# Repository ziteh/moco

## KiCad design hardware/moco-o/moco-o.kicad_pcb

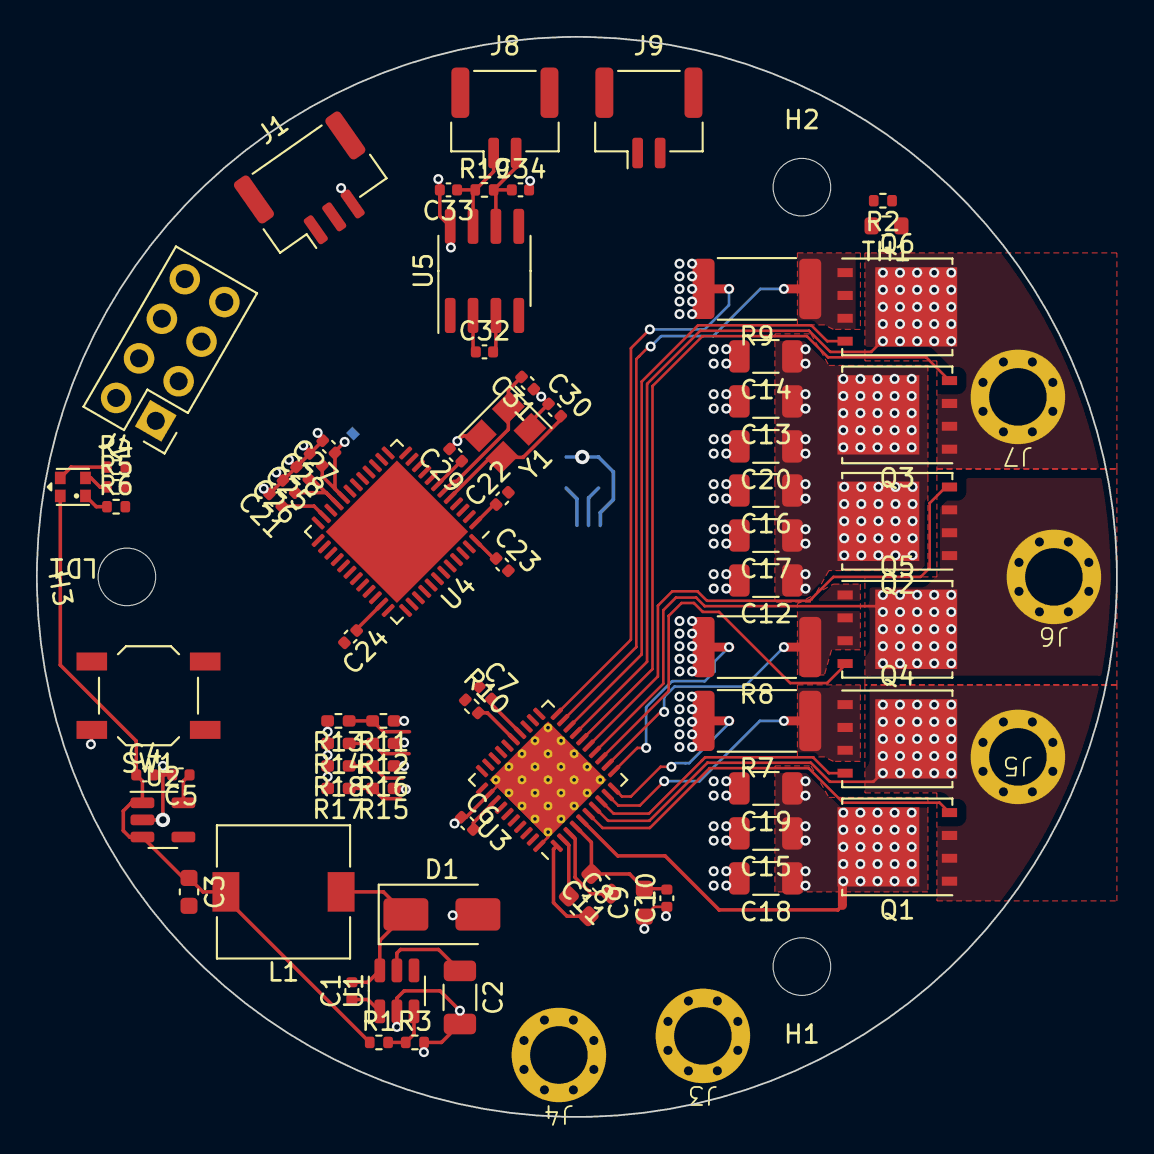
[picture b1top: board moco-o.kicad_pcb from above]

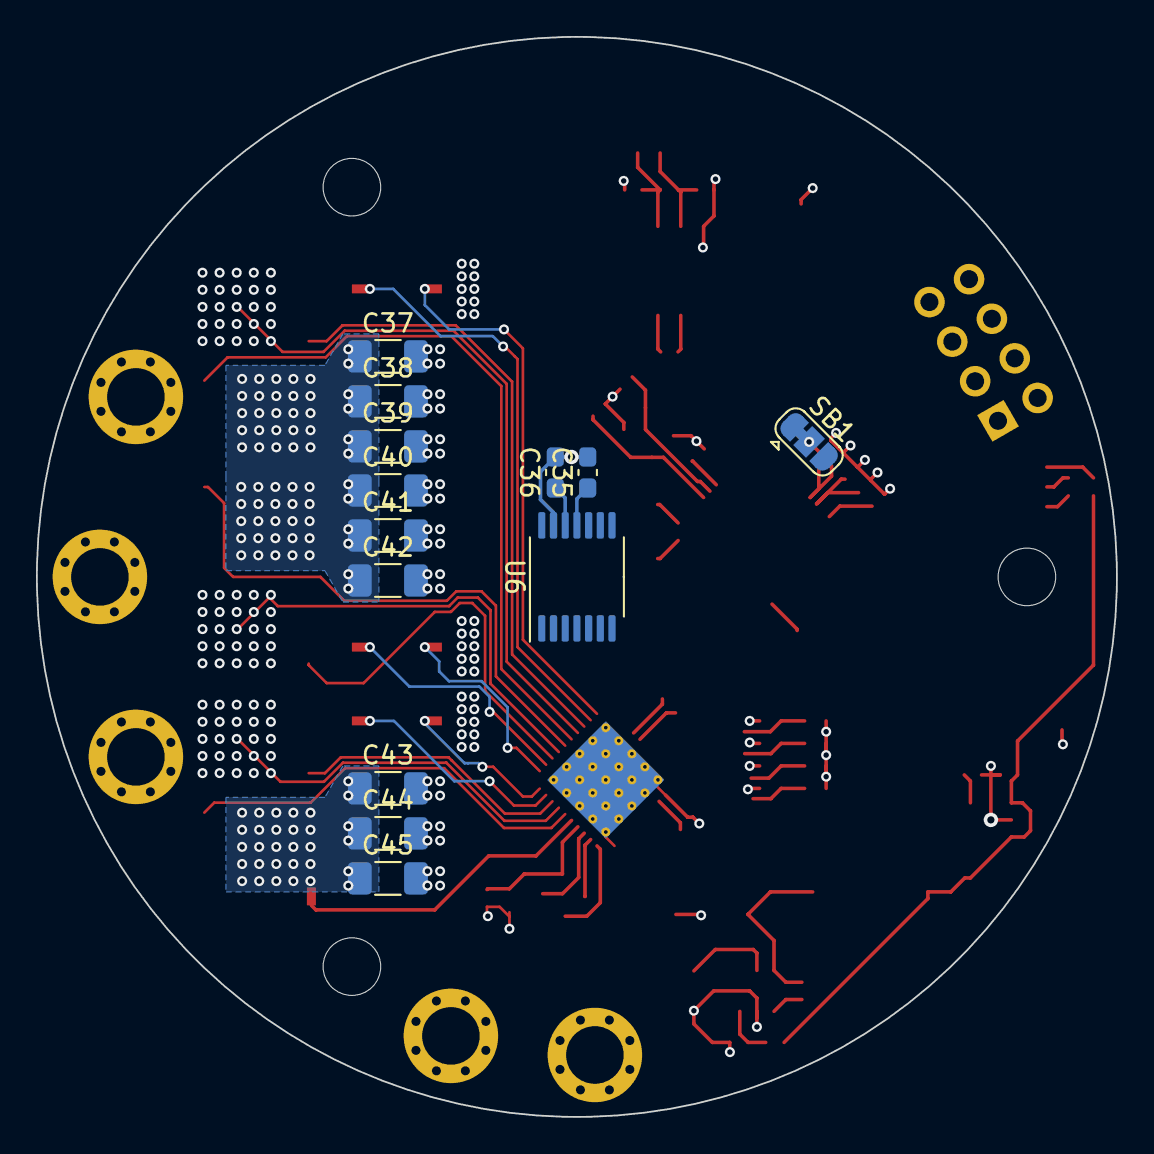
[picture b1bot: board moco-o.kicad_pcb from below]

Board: 4 copper layers, 60.0 x 60.0 mm, 102 parts (13 on the bottom side), 71 nets.

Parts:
C1, C10, C21, C22, C23, C24, C28, C29, C32: 100nF; C_0402_1005Metric
C2: 1uF/50V; C_1206_3216Metric
C3, C9: 10uF; C_0603_1608Metric
C4, C5, C26, C27: 1uF; C_0402_1005Metric
C6: 1uF/6.3V; C_0402_1005Metric
C7: 100nF/6.3V; C_0402_1005Metric
C8: 47nF; C_0603_1608Metric
C11: 1uF/16V; C_0603_1608Metric
C12, C13, C14, C15, C16, C17, C18, C19, C20: 10uF/50V; C_1206_3216Metric
C25: 10nF; C_0402_1005Metric
C30, C31: 12pF; C_0402_1005Metric
C33, C34: 30pF; C_0402_1005Metric
C35: 100nF; C_0603_1608Metric_Pad1.08x0.95mm_HandSolder
C36: 1uF; C_0603_1608Metric_Pad1.08x0.95mm_HandSolder
C37, C38, C39, C40, C41, C42, C43, C44, C45: 10uF/50V; C_1206_3216Metric_Pad1.33x1.80mm_HandSolder
D1: SS34; D_SMA
H1, H2, H3: MountingHole; MountingHole_3.2mm_M3_ISO14580
J1: Serial; JST_GH_BM03B-GHS-TBT_1x03-1MP_P1.25mm_Vertical
J2: Debug; PinHeader_2x04_P2.54mm_Vertical
J3, J4, J5: A; wire_3.2mm
J6: B; wire_3.2mm
J7: C; wire_3.2mm
J8: CAN1; JST_GH_BM02B-GHS-TBT_1x02-1MP_P1.25mm_Vertical
J9: CAN2; JST_GH_BM02B-GHS-TBT_1x02-1MP_P1.25mm_Vertical
L1: 22uH; L_7.3x7.3_H3.5
LD1: LED_BAGR; RGB LED 1.6x1.6mm
NT1, NT2, NT3, NT4, NT5, NT6, NT7: NetTie_2; NetTie-2_SMD_Pad0.5mm
Q1, Q2, Q3, Q4, Q5, Q6: CSD18540Q5B; TDSON-8-1
R1: 54.9k; R_0402_1005Metric
R2, R3, R10: 10k; R_0402_1005Metric
R4, R6: 1k; R_0402_1005Metric
R5: 5k; R_0402_1005Metric
R7, R8, R9: 0.5mΩ; R_2512_6332Metric
R11, R14, R15, R18: DNI; R_0402_1005Metric_Pad0.72x0.64mm_HandSolder
R12, R13, R16: 0R; R_0402_1005Metric_Pad0.72x0.64mm_HandSolder
R17: 47k; R_0402_1005Metric_Pad0.72x0.64mm_HandSolder
R19: 120R; R_0402_1005Metric
SB1: SolderJumper_3_Bridged12; SolderJumper-3_P1.3mm_Bridged12_RoundedPad1.0x1.5mm
SW1: RESET; SW_SPST_TL3342
TH1: NCP18XH103F03RB; R_0603_1608Metric
U1: LMR16006X; SOT-23-6
U2: RT9013-33GB; SOT-23-5
U3: DRV8323H; QFN-40-1EP_6x6mm_P0.5mm_EP4.6x4.6mm_ThermalVias
U4: STM32G431CBUx; QFN-48-1EP_7x7mm_P0.5mm_EP5.6x5.6mm
U5: TJA1050; SOIC-8_3.9x4.9mm_P1.27mm
U6: AS5047x; TSSOP-14_4.4x5mm_P0.65mm
Y1: 8MHz; Crystal_SMD_3225-4Pin_3.2x2.5mm

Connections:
+3.3V: C5.1, C21.1, C22.1, C23.1, C24.1, C25.1, C26.1, C35.1, C36.1, J2.1, R10.1, SB1.1 (A), TH1.1, U2.5 (VOUT), U4.1 (VBAT), U4.21 (VDDA), U4.23 (VDD), U4.35 (VDD), U4.48 (VDD), U6.11 (VDD), U6.12 (VDD3V3)
+5V: C3.1, C4.1, C32.2, J2.2, L1.2, LD1.2 (A), R1.1, U2.1 (VIN), U2.3 (CE), U5.3 (VCC)
/CAN Bus/CAN_H: C33.1, J8.1, J9.1, R19.1, U5.7 (CANH)
/CAN Bus/CAN_L: C34.1, J8.2, J9.2, R19.2, U5.6 (CANL)
/CAN_RX: U4.33 (PA11), U5.4 (RXD)
/CAN_TX: U4.34 (PA12), U5.1 (TXD)
/MCU/AMP_CAL: U3.31 (CAL), U4.39 (PC10)
/MCU/CS_A: U3.23 (SOA), U4.13 (PA5)
/MCU/CS_B: U3.22 (SOB), U4.14 (PA6)
/MCU/CS_C: U3.21 (SOC), U4.15 (PA7)
/MCU/GATE_ENABLE: U3.30 (ENABLE), U4.29 (PC6)
/MCU/OSC_IN: C30.2, U4.5 (PF0), Y1.3
/MCU/OSC_OUT: C31.2, U4.6 (PF1), Y1.1
/MCU/PWM_HA: U3.34 (INHA), U4.30 (PA8)
/MCU/PWM_HB: U3.36 (INHB), U4.31 (PA9)
/MCU/PWM_HC: U3.38 (INHC), U4.32 (PA10)
/MCU/PWM_LA: U3.35 (INLA), U4.26 (PB13)
/MCU/PWM_LB: U3.37 (INLB), U4.27 (PB14)
/MCU/PWM_LC: U3.39 (INLC), U4.28 (PB15)
/MCU/VREF: C7.2, SB1.3 (B), U3.24 (VREF)
/MCU/~FAULT: R10.2, U3.25 (nFAULT), U4.16 (PC4)
/Motor Driver/GAIN: R15.2, R17.1, U3.29 (GAIN)
/Motor Driver/GHA: Q1.4 (G), U3.6 (GHA)
/Motor Driver/GHB: Q2.4 (G), U3.15 (GHB)
/Motor Driver/GHC: Q3.4 (G), U3.16 (GHC)
/Motor Driver/GLA: Q4.4 (G), U3.8 (GLA)
/Motor Driver/GLB: Q5.4 (G), U3.13 (GLB)
/Motor Driver/GLC: Q6.4 (G), U3.18 (GLC)
/Motor Driver/IDRIVE: R12.2, R14.1, U3.27 (IDRIVE)
/Motor Driver/MODE: R11.2, R13.1, U3.26 (MODE)
/Motor Driver/OUTA: J5.1, Q1.1 (S), Q1.2 (S), Q1.3 (S), Q4.5 (D), U3.7 (SHA)
/Motor Driver/OUTB: J6.1, Q2.1 (S), Q2.2 (S), Q2.3 (S), Q5.5 (D), U3.14 (SHB)
/Motor Driver/OUTC: J7.1, Q3.1 (S), Q3.2 (S), Q3.3 (S), Q6.5 (D), U3.17 (SHC)
/Motor Driver/SNA: NT4.1, U3.10 (SNA)
/Motor Driver/SNB: NT5.1, U3.11 (SNB)
/Motor Driver/SNC: NT6.1, U3.20 (SNC)
/Motor Driver/SPA: NT1.1, U3.9 (SPA)
/Motor Driver/SPB: NT2.1, U3.12 (SPB)
/Motor Driver/SPC: NT3.1, U3.19 (SPC)
/Motor Driver/VDS: R16.2, R18.1, U3.28 (VDS)
/SPI_MISO: U4.42 (PB4), U6.3 (MISO)
/SPI_MOSI: U4.43 (PB5), U6.4 (MOSI)
/SPI_SCLK: U4.41 (PB3), U6.2 (CLK)
/SPI_~CS_AS5047: U4.19 (PB2), U6.1 (~CS)
/SWCLK: J2.4, U4.37 (PA14)
/SWDIO: J2.6, U4.36 (PA13)
/TEMP_SENSOR: R2.2, TH1.2, U4.25 (PB12)
/UART1_RX: J2.5, U4.45 (PB7)
/UART1_TX: J2.3, U4.44 (PB6)
/UART2_RX: J1.2, U4.11 (PA3)
/UART2_TX: J1.1, U4.10 (PA2)
/USER_LED1: R4.2, U4.17 (PB0)
/USER_LED2: R6.2, U4.18 (PB1)
/~RESET: C29.1, SW1.2, U4.7 (PG10)
GND: C2.2, C3.2, C4.2, C5.2, C6.1, C7.1, C9.1, C10.1, C12.2, C13.2, C14.2, C15.2, C16.2, C17.2, C18.2, C19.2, C20.2, C21.2, C22.2, C23.2, C24.2, C25.2, C26.2, C27.2, C28.2, C29.2, C30.1, C31.1, C32.1, C33.2, C34.2, C35.2, C36.2, C37.2, C38.2, C39.2, C40.2, C41.2, C42.2, C43.2, C44.2, C45.2, D1.2 (A), J1.3, J2.7, J2.8, J4.1, NT4.2, NT5.2, NT6.2, R2.1, R3.2, R5.2, R7.2, R8.2, R9.2, R13.2, R14.2, R17.2, R18.2, SW1.1, U1.2 (GND), U2.2 (GND), U3.32 (AGND), U3.40 (PGND), U3.41 (GND), U4.49 (VSS), U5.2 (GND), U5.8 (S), U6.5 (TST), U6.13 (GND), Y1.2, Y1.4
unnamed: C1.2, D1.1 (K), L1.1, U1.6 (SW)
unnamed: LD1.1 (BK), R6.1
unnamed: LD1.3 (GK), R5.1
unnamed: LD1.4 (RK), R4.1
unnamed: NT1.2, Q4.1 (S), Q4.2 (S), Q4.3 (S), R7.1
unnamed: NT2.2, Q5.1 (S), Q5.2 (S), Q5.3 (S), R8.1
unnamed: NT3.2, Q6.1 (S), Q6.2 (S), Q6.3 (S), R9.1
unnamed: C27.1, C28.1, SB1.2 (C), U4.20 (VREF+)
unnamed: C1.1, U1.1 (CB)
unnamed: R1.2, R3.1, U1.3 (FB)
unnamed: C8.1, U3.2 (CPH)
unnamed: C8.2, U3.1 (CPL)
unnamed: C11.1, U3.3 (VCP)
unnamed: NT7.2, U3.5 (VDRAIN)
VDD: C6.2, R11.1, R12.1, R15.1, R16.1, U3.33 (DVDD)
Vdrive: C2.1, C9.2, C10.2, C11.2, C12.1, C13.1, C14.1, C15.1, C16.1, C17.1, C18.1, C19.1, C20.1, C37.1, C38.1, C39.1, C40.1, C41.1, C42.1, C43.1, C44.1, C45.1, J3.1, NT7.1, Q1.5 (D), Q2.5 (D), Q3.5 (D), U1.5 (VIN), U3.4 (VM)

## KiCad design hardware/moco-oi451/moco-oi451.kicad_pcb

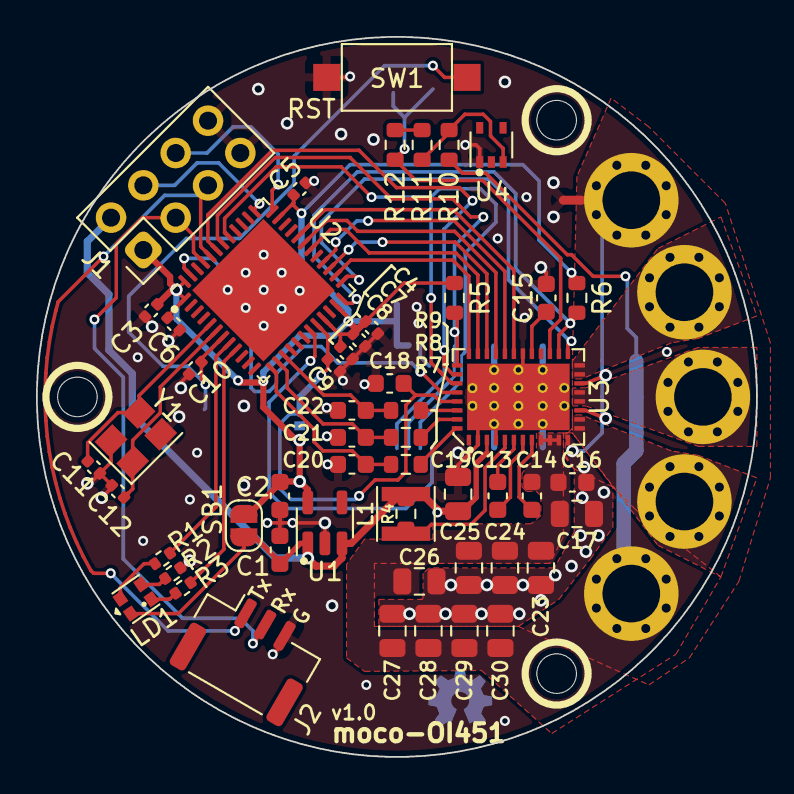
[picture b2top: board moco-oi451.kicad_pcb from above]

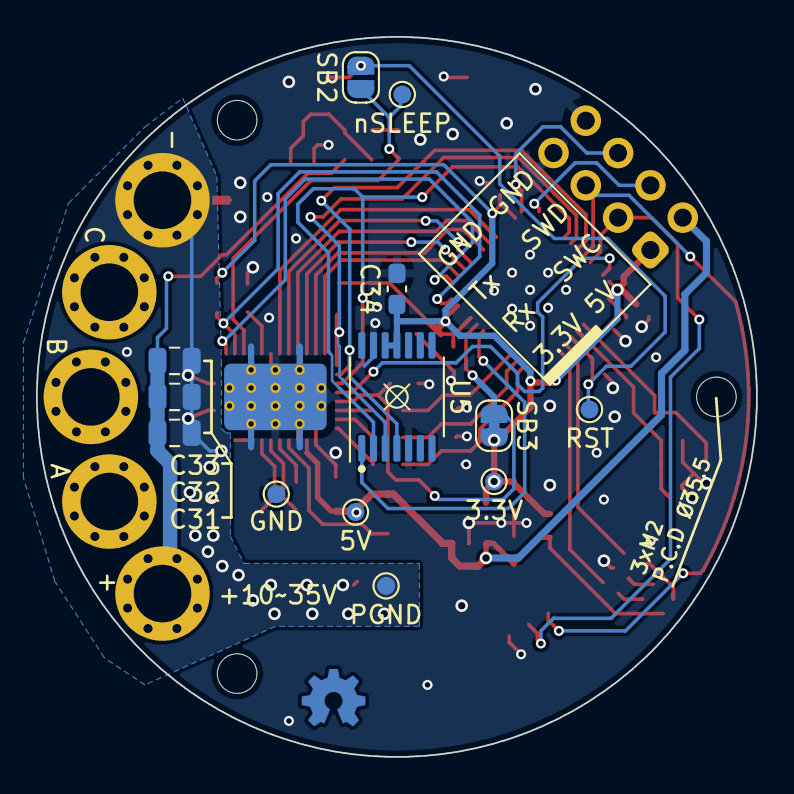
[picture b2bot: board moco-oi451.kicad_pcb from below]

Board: 2 copper layers, 40.0 x 40.0 mm, 75 parts (13 on the bottom side), 48 nets.

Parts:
C1, C2: 1uF; C_0603_1608Metric
C3, C4, C5, C6, C9, C10: 100nF; C_0402_1005Metric
C7: 10nF; C_0402_1005Metric
C8: 1uF; C_0402_1005Metric
C11, C12: 12pF; C_0402_1005Metric
C13: 47nF/100V; C_0603_1608Metric
C14: 1uF/16V; C_0603_1608Metric
C15: 1uF/6.3V; C_0603_1608Metric
C16: 100nF/50V; C_0603_1608Metric
C17, C23, C24, C25, C26, C27, C28, C29, C30, C31, C32, C33: 10uF/50V; C_0805_2012Metric
C18: 100nF/6.3V; C_0603_1608Metric
C19: 22uF/16V; C_0805_2012Metric
C20, C21, C22: 22pF; C_0603_1608Metric
C34: 100nF; C_0603_1608Metric_Pad1.08x0.95mm_HandSolder
H1, H2, H3: MountingHole; MountingHole_2.2mm_M2_ISO14580
J1: Debug; PinHeader_2x04_P2.54mm_Vertical
J2: Serial; JST_GH_SM03B-GHS-TB_1x03-1MP_P1.25mm_Horizontal
J3: V+; wire_3.2mm
J4: V-; wire_3.2mm
J5: A; wire_3.2mm
J6: B; wire_3.2mm
J7: C; wire_3.2mm
L1: 47uH; L_Taiyo-Yuden_MD-3030
LD1: LED_BAGR; RGB LED 1.6x1.6mm
NT1: NetTie_2; NetTie-2_SMD_Pad0.5mm
R1, R3: 1k; R_0402_1005Metric
R2: 5k; R_0402_1005Metric
R4: 22R; R_0603_1608Metric
R5, R6: 5.1k; R_0603_1608Metric
R7, R8, R9: 330R; R_0603_1608Metric
R10: 10k/100mW; R_0603_1608Metric
R11, R12: 10k; R_0603_1608Metric
SB1, SB2: SolderJumper_2_Open; SolderJumper-2_P1.3mm_Open_RoundedPad1.0x1.5mm
SB3: SolderJumper_2_Bridged; SolderJumper-2_P1.3mm_Bridged_RoundedPad1.0x1.5mm
SW1: RESET; SW_SPST_CK_RS282G05A3
TP1: ~{RESET}; TestPoint_Pad_D1.0mm
TP2: V_{CC}; TestPoint_Pad_D1.0mm
TP3: GND; TestPoint_Pad_D1.0mm
TP4: V_{BK}; TestPoint_Pad_D1.0mm
TP5: PGND; TestPoint_Pad_D1.0mm
TP6: nSLEEP; TestPoint_Pad_D1.0mm
U1: RT9013-33GB; SOT-23-5
U2: STM32G431CBUx; QFN-48-1EP_7x7mm_P0.5mm_EP5.6x5.6mm
U3: DRV8316CR; VQFN-40_RGF_5x7mm_0.5mm_pitch_thermalpad
U4: LM4040A50; SOT-353_SC-70-5
U5: AS5047x; TSSOP-14_4.4x5mm_P0.65mm
Y1: 8MHz; Crystal_SMD_3225-4Pin_3.2x2.5mm

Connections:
+3.3V: C2.1, C3.1, C4.1, C5.1, C6.1, C7.1, C8.1, C34.2, J1.1, R5.1, R6.1, SB1.2 (B), SB3.2 (B), TP2.1, U1.5 (VOUT), U2.1 (VBAT), U2.21 (VDDA), U2.23 (VDD), U2.35 (VDD), U2.48 (VDD), U5.11 (VDD), U5.12 (VDD3V3)
+5V: C1.1, C19.2, J1.2, L1.2, LD1.2 (A), R4.2, SB1.1 (A), TP4.1, U1.1 (VIN), U1.3 (EN), U3.3 (FB_BK)
/ Rotary Sensor/MISO: R5.2, U2.42 (PB4), U3.33 (SDO), U5.3 (MISO)
/ Rotary Sensor/MOSI: U2.43 (PB5), U3.34 (SDI), U5.4 (MOSI)
/ Rotary Sensor/SCLK: U2.41 (PB3), U3.35 (SCLK), U5.2 (CLK)
/ Rotary Sensor/~CS: U2.19 (PB2), U5.1 (~CS)
/Driver/AVDD: C15.2, U3.25 (AVDD)
/Driver/DRVOFF: U2.25 (PB12), U3.21 (DRVOFF)
/Driver/INHA: U2.32 (PA10), U3.27 (INHA)
/Driver/INHB: U2.31 (PA9), U3.29 (INHB)
/Driver/INHC: U2.30 (PA8), U3.31 (INHC)
/Driver/INLA: U2.28 (PB15), U3.28 (INLA)
/Driver/INLB: U2.27 (PB14), U3.30 (INLB)
/Driver/INLC: U2.26 (PB13), U3.32 (INLC)
/Driver/OUTA: J5.1, U3.13 (OUTA), U3.14 (OUTA)
/Driver/OUTB: J6.1, U3.16 (OUTB), U3.17 (OUTB)
/Driver/OUTC: J7.1, U3.19 (OUTC), U3.20 (OUTC)
/Driver/SOA: C20.1, R7.1, U2.13 (PA5)
/Driver/SOB: C21.1, R8.1, U2.14 (PA6)
/Driver/SOC: C22.1, R9.1, U2.15 (PA7)
/Driver/V_{REF}: C9.1, C18.1, SB3.1 (A), U2.20 (VREF+), U3.37 (VREF/LILM)
/Driver/~CS: U2.47 (PB9), U3.36 (nSCS)
/Driver/~FAULT: R6.2, U2.24 (PB11), U3.22 (nFAULT)
/Driver/~SLEEP: R12.2, SB2.1 (A), TP6.1, U3.23 (nSLEEP)
/MCU/OSC_IN: C11.2, U2.5 (PF0), Y1.3
/MCU/OSC_OUT: C12.2, U2.6 (PF1), Y1.1
/SWCLK: J1.4, U2.37 (PA14)
/SWDIO: J1.6, U2.36 (PA13)
/UART1_RX: J1.3, J2.2, U2.45 (PB7)
/UART1_TX: J1.5, J2.1, U2.44 (PB6)
/USER_LED1: R1.2, U2.8 (PA0)
/USER_LED2: R3.2, U2.9 (PA1)
/~RESET: C10.1, SB2.2 (B), SW1.2, TP1.1, U2.7 (PG10)
GND: C1.2, C2.2, C3.2, C4.2, C5.2, C6.2, C7.2, C8.2, C9.2, C10.2, C11.1, C12.1, C15.1, C18.2, C19.1, C20.2, C21.2, C22.2, C34.1, J1.7, J1.8, J2.3, NT1.2, R2.2, SW1.1, TP3.1, U1.2 (GND), U2.49 (VSS), U3.2 (AGND), U3.4 (GND_BK), U3.26 (AGND), U3.41 (EP), U4.1 (A), U5.5 (TST), U5.13 (GND), Y1.2, Y1.4
GNDPWR: C16.1, C17.1, C23.2, C24.2, C25.2, C26.2, C27.2, C28.2, C29.2, C30.2, C31.2, C32.2, C33.2, J4.1, NT1.1, TP5.1, U3.12 (PGND), U3.15 (PGND), U3.18 (PGND)
unnamed: LD1.1 (BK), R3.1
unnamed: LD1.3 (GK), R2.1
unnamed: LD1.4 (RK), R1.1
unnamed: R11.2, R12.1
unnamed: C14.1, U3.8 (CP)
unnamed: C13.2, U3.7 (CPH)
unnamed: C13.1, U3.6 (CPL)
unnamed: R7.2, U3.40 (SOA)
unnamed: R8.2, U3.39 (SOB)
unnamed: R9.2, U3.38 (SOC)
unnamed: L1.1, R4.1, U3.5 (SW_BK)
unnamed: R10.2, R11.1, U4.3 (K)
Vdrive: C14.2, C16.2, C17.2, C23.1, C24.1, C25.1, C26.1, C27.1, C28.1, C29.1, C30.1, C31.1, C32.1, C33.1, J3.1, R10.1, U3.9 (VM), U3.10 (VM), U3.11 (VM)

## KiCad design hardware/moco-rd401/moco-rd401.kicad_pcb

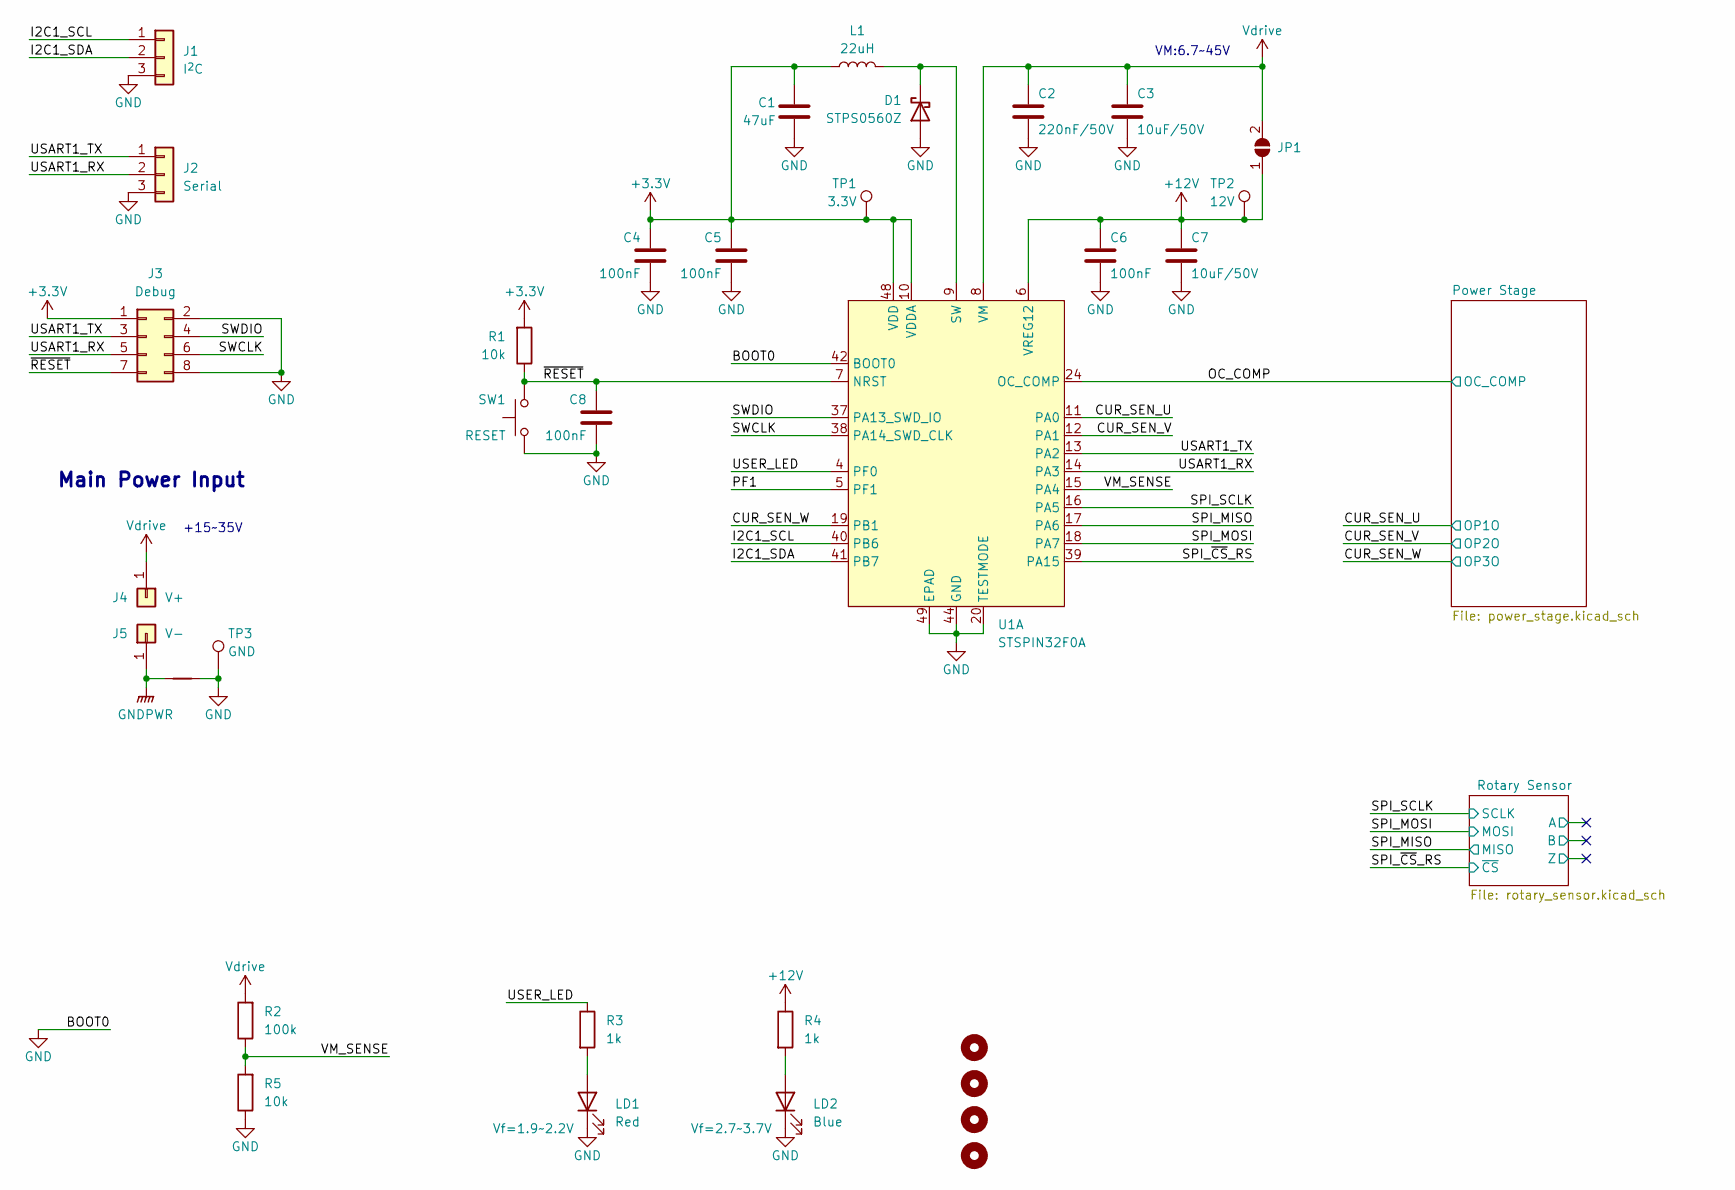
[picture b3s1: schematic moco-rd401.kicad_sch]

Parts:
C1: 47uF; C_0805_2012Metric; MFR. Part# CL21A476MQYNNNE; LCSC C16780
C2: 220nF/50V; C_0805_2012Metric; MFR. Part# CL21B224KBFNNNE; LCSC C5378
C3, C7: 10uF/50V; C_0805_2012Metric; MFR. Part# GRM21BR61H106KE43L; LCSC C440198
C4, C5, C6, C8: 100nF; C_0402_1005Metric; MFR. Part# CL05B104KB54PNC; LCSC C307331
D1: STPS0560Z; D_SOD-123F; MFR. Part# STPS0560Z; LCSC C99285
H1, H2, H3, H4: MountingHole; MountingHole_2.2mm_M2_ISO14580
J1: I^{2}C; JST_SH_SM03B-SRSS-TB_1x03-1MP_P1.00mm_Horizontal; MFR. Part# SM03B-SRSS-TB(LF)(SN); LCSC C160403
J2: Serial; JST_SH_SM03B-SRSS-TB_1x03-1MP_P1.00mm_Horizontal; MFR. Part# SM03B-SRSS-TB(LF)(SN); LCSC C160403
J3: Debug; PinHeader_2x04_P2.54mm_Vertical
J4: V+; wire_2.2mm
J5: V-; wire_2.2mm
JP1: SolderJumper_2_Open; SolderJumper-2_P1.3mm_Open_RoundedPad1.0x1.5mm
L1: 22uH; L_Taiyo-Yuden_MD-3030; MFR. Part# YNR3015-220M; LCSC C497564
LD1: Red; LED_0603_1608Metric; MFR. Part# KT-0603R; LCSC C2286
LD2: Blue; LED_0603_1608Metric; MFR. Part# 19-217/GHC-YR1S2/3T; LCSC C72043
NT1: NetTie_2; NetTie-2_SMD_Pad0.5mm
R1, R5: 10k; R_0402_1005Metric; MFR. Part# 0402WGF1002TCE; LCSC C25744
R2: 100k; R_0402_1005Metric; MFR. Part# 0402WGF1003TCE; LCSC C25741
R3, R4: 1k; R_0402_1005Metric; MFR. Part# 0402WGF1001TCE; LCSC C11702
SW1: RESET; SW_SPST_EVQP7C; MFR. Part# 3*4mm
TP1: 3.3V; TestPoint_Pad_D1.0mm
TP2: 12V; TestPoint_Pad_D1.0mm
TP3: GND; TestPoint_Pad_D1.0mm
U1: STSPIN32F0A; VFQFN-48_7x7_EP2.8mm_Pitch0.5mm; MFR. Part# STSPIN32F0A; LCSC C1520987

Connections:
+3.3V: C1.1, C4.1, C5.1, J3.1, L1.1, R1.2, TP1.1, U1.10 (VDDA), U1.48 (VDD); also elsewhere on the board
+12V: C6.1, C7.1, JP1.1 (A), R4.1, TP2.1, U1.6 (VREG12)
/CUR_SEN_U: U1.11 (PA0); also elsewhere on the board
/CUR_SEN_V: U1.12 (PA1); also elsewhere on the board
/CUR_SEN_W: U1.19 (PB1); also elsewhere on the board
/I2C1_SCL: J1.1, U1.40 (PB6)
/I2C1_SDA: J1.2, U1.41 (PB7)
/OC_COMP: U1.24 (OC_COMP); also elsewhere on the board
/PF1: U1.5 (PF1)
/SPI_MISO: U1.17 (PA6); also elsewhere on the board
/SPI_MOSI: U1.18 (PA7); also elsewhere on the board
/SPI_SCLK: U1.16 (PA5); also elsewhere on the board
/SPI_~CS_RS: U1.39 (PA15); also elsewhere on the board
/SWCLK: J3.6, U1.38 (PA14_SWD_CLK)
/SWDIO: J3.4, U1.37 (PA13_SWD_IO)
/USART1_RX: J2.2, J3.5, U1.14 (PA3)
/USART1_TX: J2.1, J3.3, U1.13 (PA2)
/USER_LED: R3.1, U1.4 (PF0)
/VM_SENSE: R2.1, R5.2, U1.15 (PA4)
/~RESET: C8.1, J3.7, R1.1, SW1.1, U1.7 (NRST)
GND: C1.2, C2.2, C3.2, C4.2, C5.2, C6.2, C7.2, C8.2, D1.2 (A), J1.3, J2.3, J3.2, J3.8, LD1.1 (K), LD2.1 (K), NT1.2, R5.1, SW1.2, TP3.1, U1.20 (TESTMODE), U1.42 (BOOT0), U1.44 (GND), U1.49 (EPAD); also elsewhere on the board
GNDPWR: J5.1, NT1.1; also elsewhere on the board
unnamed: D1.1 (K), L1.2, U1.9 (SW)
unnamed: LD1.2 (A), R3.2
unnamed: LD2.2 (A), R4.2
Vdrive: C2.1, C3.1, J4.1, JP1.2 (B), R2.2, U1.8 (VM); also elsewhere on the board

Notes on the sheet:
+15~35V
VM:6.7~45V
Main Power Input

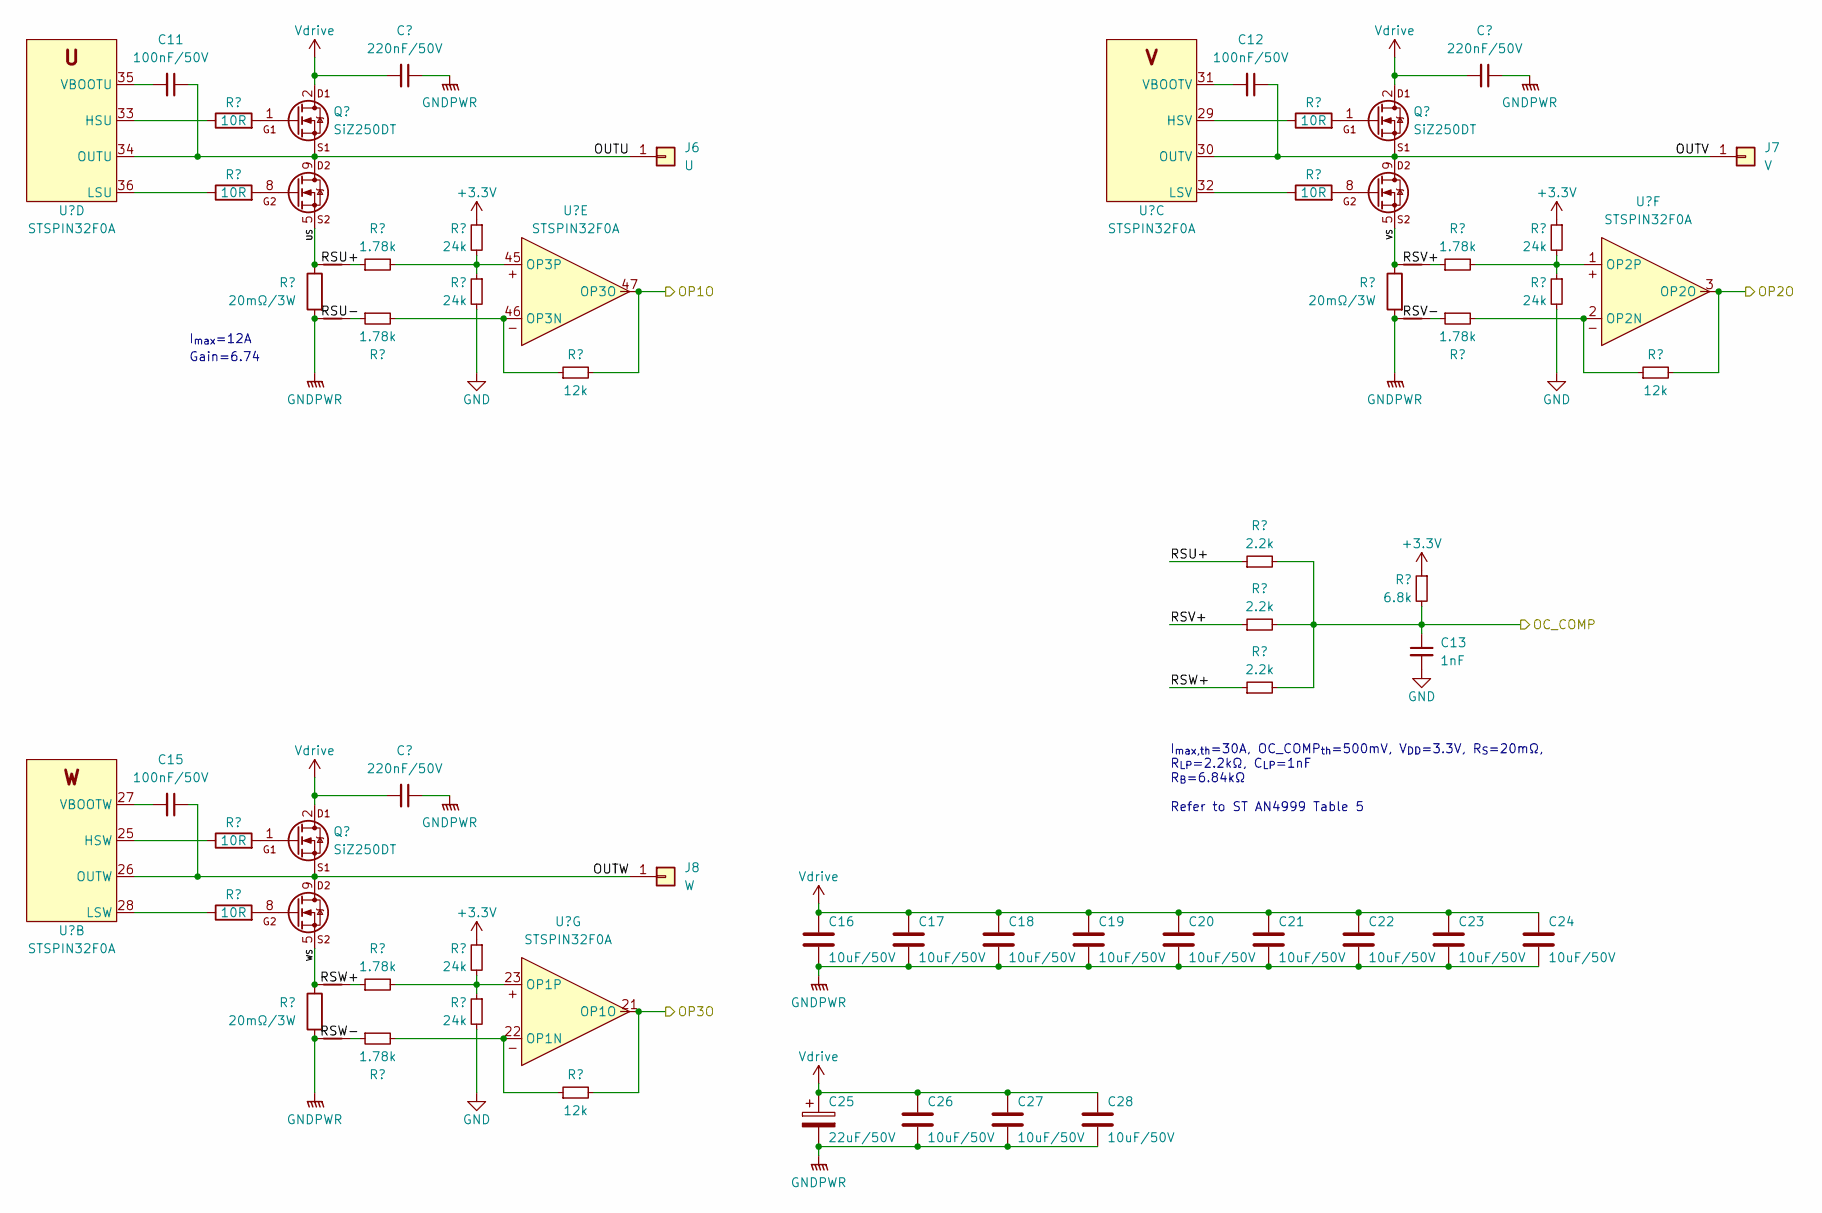
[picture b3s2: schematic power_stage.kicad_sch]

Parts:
C9, C10, C14: 220nF/50V; C_0805_2012Metric; MFR. Part# CL21B224KBFNNNE; LCSC C5378
C11, C12, C15: 100nF/50V; C_0402_1005Metric; MFR. Part# CL05B104KB54PNC; LCSC C307331
C13: 1nF; C_0402_1005Metric; MFR. Part# 0402B102K500NT; LCSC C1523
C16, C17, C18, C19, C20, C21, C22, C23, C24, C26, C27, C28: 10uF/50V; C_0805_2012Metric; MFR. Part# GRM21BR61H106KE43L; LCSC C440198
C25: 22uF/50V; CP_Elec_5x5.8; MFR. Part# EEEFT1H220AR; LCSC C336246
J6: U; wire_2.2mm
J7: V; wire_2.2mm
J8: W; wire_2.2mm
NT2, NT3, NT4, NT5, NT6, NT7: NetTie_2; NetTie-2_SMD_Pad0.5mm
Q1, Q2, Q3: SiZ250DT; PowerPAIR_3x3S_TP; MFR. Part# SIZ250DT-T1-GE3; LCSC C3279427
R6, R7, R8, R9, R26, R27: 10R; R_0402_1005Metric; MFR. Part# 0402WGF100JTCE; LCSC C25077
R10, R11, R15, R17, R28, R31: 24k; R_0402_1005Metric; MFR. Part# 0402WGF2402TCE; LCSC C25769
R12, R13, R18, R19, R29, R32: 1.78k; R_0402_1005Metric; MFR. Part# ARG02FTC1781; LCSC C284379
R14, R16, R30: 20mΩ/3W; R_2512_6332Metric; MFR. Part# CRA2512-FZ-R020ELF; LCSC C840620
R20, R21, R33: 12k; R_0402_1005Metric; MFR. Part# 0402WGF1202TCE; LCSC C25752
R22, R24, R25: 2.2k; R_0402_1005Metric; MFR. Part# 0402WGF2201TCE; LCSC C25879
R23: 6.8k; R_0402_1005Metric; MFR. Part# 0402WGF6801TCE; LCSC C25917
U1: STSPIN32F0A; VFQFN-48_7x7_EP2.8mm_Pitch0.5mm; MFR. Part# STSPIN32F0A; LCSC C1520987

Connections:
+3.3V: R10.1, R11.1, R23.1, R28.1; also elsewhere on the board
/CUR_SEN_U: R20.2, U1.47 (OP3O); also elsewhere on the board
/CUR_SEN_V: R21.2, U1.3 (OP2O); also elsewhere on the board
/CUR_SEN_W: R33.2, U1.21 (OP1O); also elsewhere on the board
/OC_COMP: C13.1, R22.2, R23.2, R24.2, R25.2; also elsewhere on the board
/Power Stage/OUTU: C11.1, J6.1, Q1.9 (S1D2), U1.34 (OUTU)
/Power Stage/OUTV: C12.1, J7.1, Q2.9 (S1D2), U1.30 (OUTV)
/Power Stage/OUTW: C15.1, J8.1, Q3.9 (S1D2), U1.26 (OUTW)
/Power Stage/RSU+: NT2.1, R12.1, R22.1
/Power Stage/RSU-: NT4.1, R18.1
/Power Stage/RSV+: NT3.1, R13.1, R24.1
/Power Stage/RSV-: NT5.1, R19.1
/Power Stage/RSW+: NT6.1, R25.1, R29.1
/Power Stage/RSW-: NT7.1, R32.1
/Power Stage/US: NT2.2, Q1.5 (S2), Q1.6 (S2), Q1.7 (S2), R14.1
/Power Stage/VS: NT3.2, Q2.5 (S2), Q2.6 (S2), Q2.7 (S2), R16.1
/Power Stage/WS: NT6.2, Q3.5 (S2), Q3.6 (S2), Q3.7 (S2), R30.1
GND: C13.2, R15.2, R17.2, R31.2; also elsewhere on the board
GNDPWR: C9.1, C10.1, C14.1, C16.2, C17.2, C18.2, C19.2, C20.2, C21.2, C22.2, C23.2, C24.2, C25.2, C26.2, C27.2, C28.2, NT4.2, NT5.2, NT7.2, R14.2, R16.2, R30.2; also elsewhere on the board
unnamed: Q1.1 (G1), R6.2
unnamed: Q1.8 (G2), R8.2
unnamed: Q2.1 (G1), R7.2
unnamed: Q2.8 (G2), R9.2
unnamed: Q3.1 (G1), R26.2
unnamed: Q3.8 (G2), R27.2
unnamed: R26.1, U1.25 (HSW)
unnamed: R27.1, U1.28 (LSW)
unnamed: C15.2, U1.27 (VBOOTW)
unnamed: R7.1, U1.29 (HSV)
unnamed: R9.1, U1.32 (LSV)
unnamed: C12.2, U1.31 (VBOOTV)
unnamed: R6.1, U1.33 (HSU)
unnamed: R8.1, U1.36 (LSU)
unnamed: C11.2, U1.35 (VBOOTU)
unnamed: R18.2, R20.1, U1.46 (OP3N)
unnamed: R10.2, R12.2, R15.1, U1.45 (OP3P)
unnamed: R19.2, R21.1, U1.2 (OP2N)
unnamed: R11.2, R13.2, R17.1, U1.1 (OP2P)
unnamed: R32.2, R33.1, U1.22 (OP1N)
unnamed: R28.2, R29.2, R31.1, U1.23 (OP1P)
Vdrive: C9.2, C10.2, C14.2, C16.1, C17.1, C18.1, C19.1, C20.1, C21.1, C22.1, C23.1, C24.1, C25.1, C26.1, C27.1, C28.1, Q1.2 (D1), Q1.3 (D1), Q1.4 (D1), Q1.10 (D1), Q2.2 (D1), Q2.3 (D1), Q2.4 (D1), Q2.10 (D1), Q3.2 (D1), Q3.3 (D1), Q3.4 (D1), Q3.10 (D1); also elsewhere on the board

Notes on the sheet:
Gain=6.74
I_{max,th}=30A, OC_COMP_{th}=500mV, V_{DD}=3.3V, R_{S}=20mΩ, R_{LP}=2.2kΩ, C_{LP}=1nF R_{B}=6.84kΩ Refer to ST AN4999 Table 5
I_{max}=12A

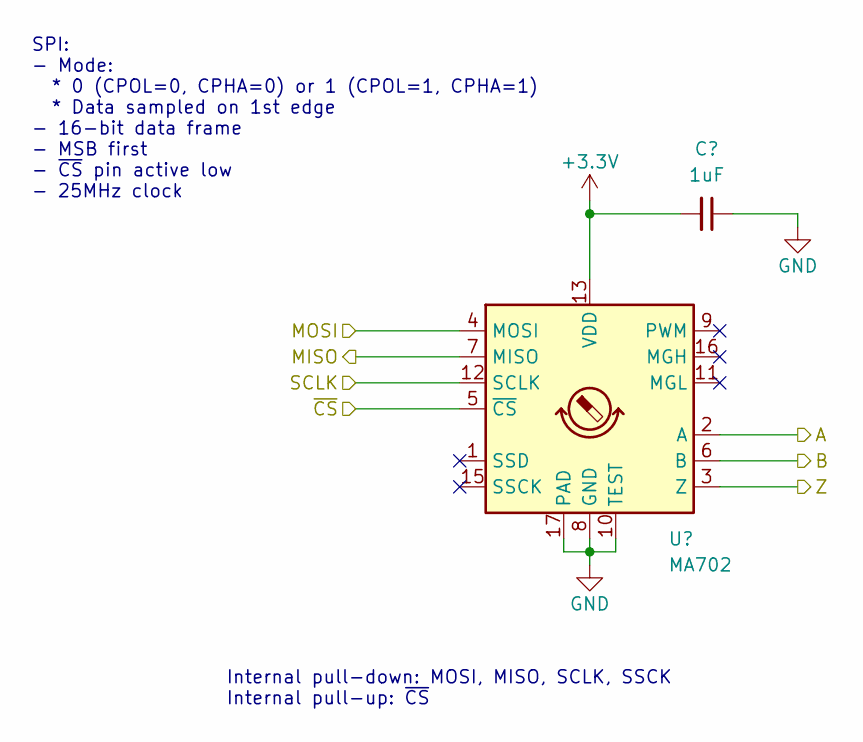
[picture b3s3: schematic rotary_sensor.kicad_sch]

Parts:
C29: 1uF; C_0402_1005Metric; MFR. Part# CL05A105KA5NQNC; LCSC C52923
U2: MA702; QFN-16-1EP_3x3mm_P0.5mm_EP1.75x1.75mm; MFR. Part# MA702GQ-Z

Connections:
+3.3V: C29.2, U2.13 (VDD); also elsewhere on the board
/ Rotary Sensor/A: U2.2 (A)
/ Rotary Sensor/B: U2.6 (B)
/ Rotary Sensor/Z: U2.3 (Z)
/SPI_MISO: U2.7 (MISO); also elsewhere on the board
/SPI_MOSI: U2.4 (MOSI); also elsewhere on the board
/SPI_SCLK: U2.12 (SCLK); also elsewhere on the board
/SPI_~CS_RS: U2.5 (~CS); also elsewhere on the board
GND: C29.1, U2.8 (GND), U2.10 (TEST), U2.17 (PAD); also elsewhere on the board

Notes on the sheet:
Internal pull-down: MOSI, MISO, SCLK, SSCK Internal pull-up: ~{CS}
SPI: - Mode: * 0 (CPOL=0, CPHA=0) or 1 (CPOL=1, CPHA=1) * Data sampled on 1st edge - 16-bit data frame - MSB first - ~{CS} pin active low - 25MHz clock

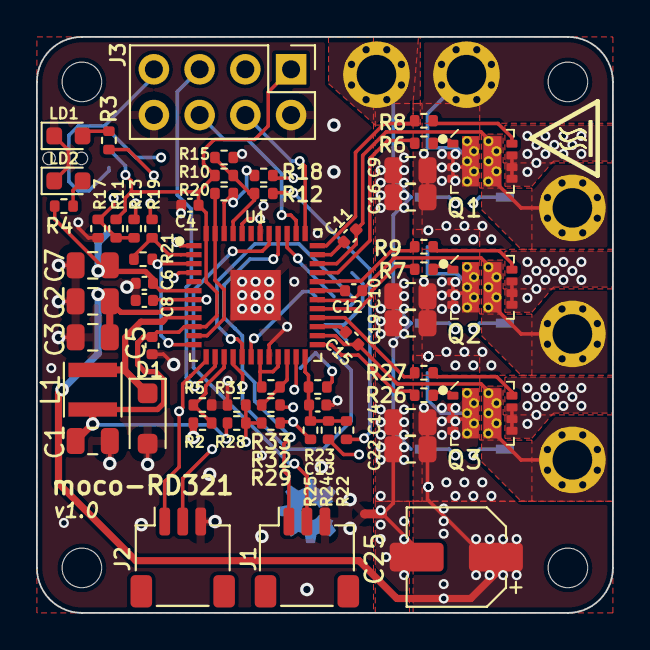
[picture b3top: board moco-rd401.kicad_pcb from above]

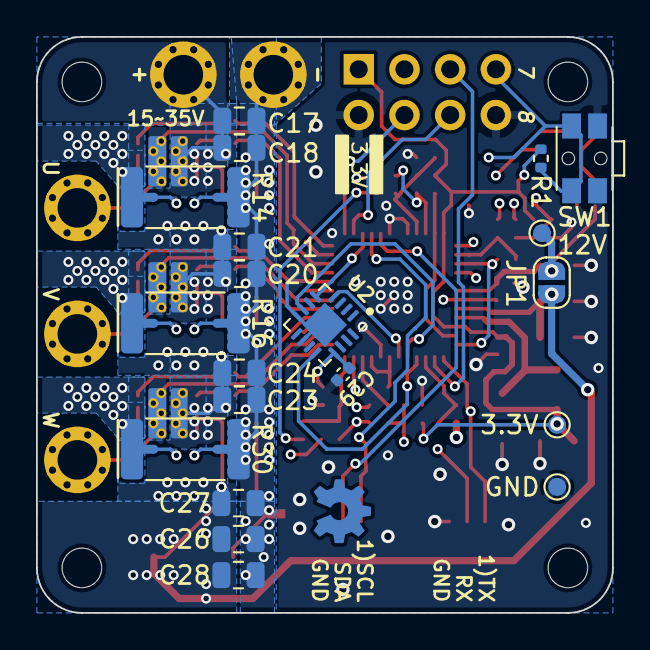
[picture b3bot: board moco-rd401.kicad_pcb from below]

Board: 4 copper layers, 32.0 x 32.0 mm, 95 parts (26 on the bottom side), 58 nets.

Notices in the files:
hardware/moco-oi451/moco-oi451.kicad_pcb:
MIT license (Open source hardware)
